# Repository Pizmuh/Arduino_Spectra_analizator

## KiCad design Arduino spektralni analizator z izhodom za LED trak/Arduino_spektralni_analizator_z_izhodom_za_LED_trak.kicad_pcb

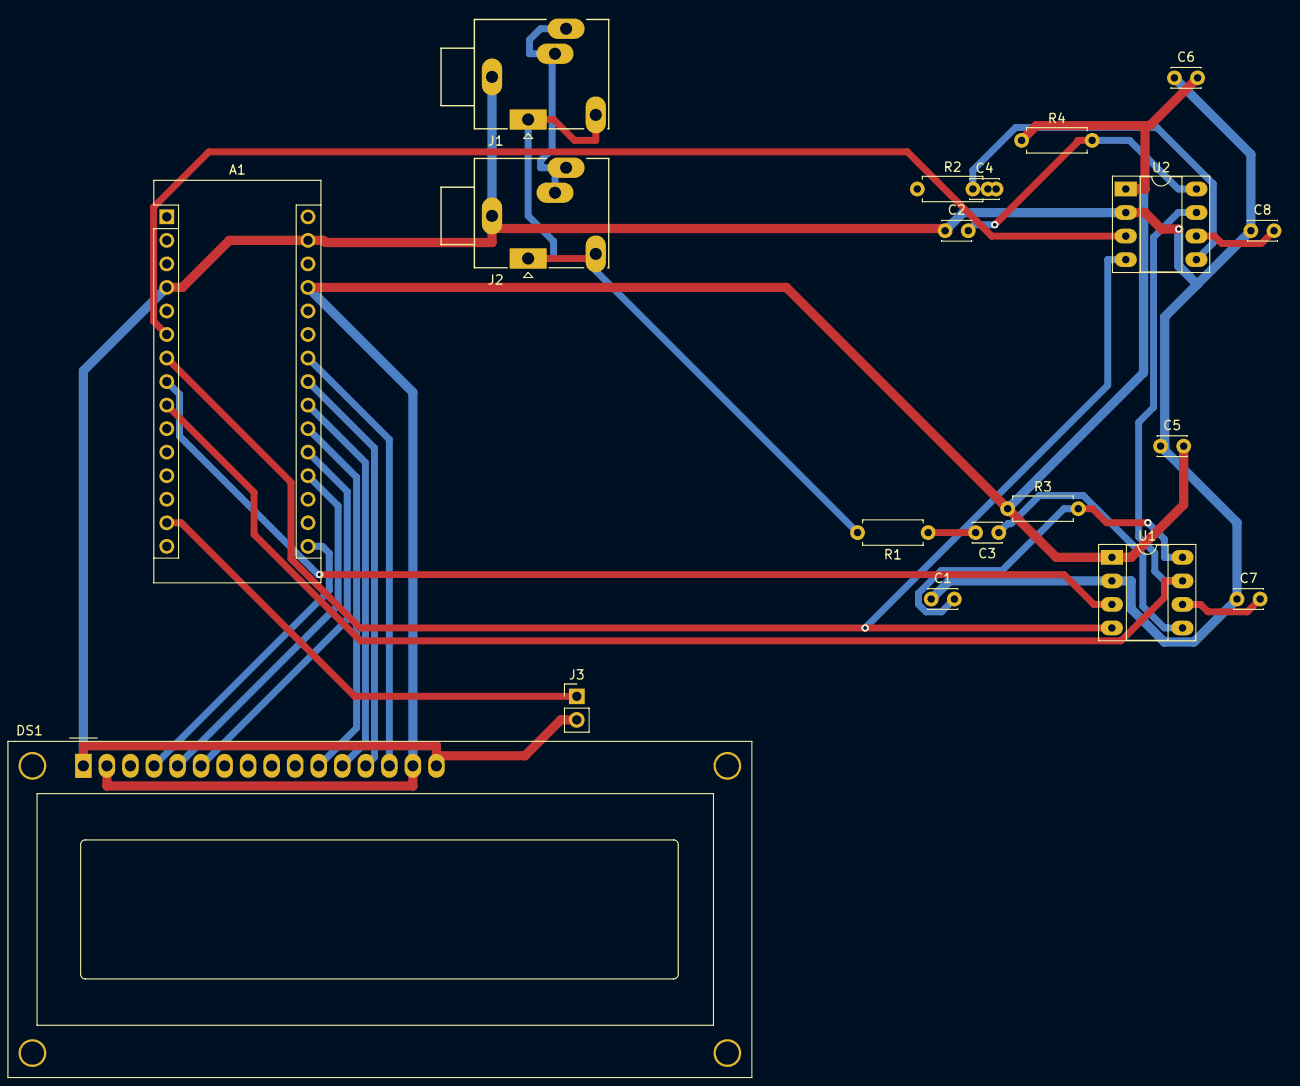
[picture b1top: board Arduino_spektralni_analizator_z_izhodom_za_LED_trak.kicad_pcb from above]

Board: 2 copper layers, 19 parts (0 on the bottom side), 24 nets.

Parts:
A1: Arduino_Nano_v3.x; Arduino_Nano
C1, C2: 33pF; C_Disc_D3.0mm_W2.0mm_P2.50mm
C3, C4: 10nF; C_Disc_D3.0mm_W2.0mm_P2.50mm
C5, C6: 0.1uF; C_Disc_D3.0mm_W2.0mm_P2.50mm
C7, C8: 0.1 uF; C_Disc_D3.0mm_W2.0mm_P2.50mm
DS1: WC1602A
J1, J2: AudioJack3_SwitchTR; Jack_3.5mm_Ledino_KB3SPRS_Horizontal
J3: Conn_01x02_Male; PinHeader_1x02_P2.54mm_Vertical
R1, R2: 22k; R_Axial_DIN0207_L6.3mm_D2.5mm_P7.62mm_Horizontal
R3, R4: 200k; R_Axial_DIN0207_L6.3mm_D2.5mm_P7.62mm_Horizontal
U1, U2: MSGEQ7; DIP-8_W7.62mm_Socket_LongPads

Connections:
/LCD_D4: A1.21 (A2), DS1.11 (D4)
/LCD_D5: A1.22 (A3), DS1.12 (D5)
/LCD_D6: A1.23 (A4), DS1.13 (D6)
/LCD_D7: A1.24 (A5), DS1.14 (D7)
/LCD_EN: A1.20 (A1), DS1.6 (E)
/LCD_RS: A1.16 (D13), DS1.4 (RS)
/LCD_RW: A1.19 (A0), DS1.5 (R/W)
/MSGEQ7_DATA_L: A1.6 (D3), U2.3 (OUT)
/MSGEQ7_DATA_R: A1.8 (D5), U1.3 (OUT)
/MSGEQ7_RESET: A1.9 (D6), U1.7 (RESET), U2.7 (RESET)
/MSGEQ7_STROBE: A1.7 (D4), U1.4 (STROBE), U2.4 (STROBE)
/SPK_LEFT: J1.R, J1.RN, J2.R, J2.RN, R2.2
/SPK_RIGHT: J1.T, J1.TN, J2.T, J2.TN, R1.2
/WS2813_DRIVE: A1.14 (D11), J3.1
GND: A1.4 (GND), A1.29 (GND), C1.1, C2.1, C5.1, C6.1, C7.1, C8.1, DS1.1 (VSS), DS1.16 (LED(-)), J1.S, J2.S, J3.2, U1.2 (VSS), U2.2 (VSS)
unnamed: C1.2, R3.2, U1.8 (CKIN)
unnamed: C2.2, R4.2, U2.8 (CKIN)
unnamed: C3.1, U1.5 (IN)
unnamed: C3.2, R1.1
unnamed: C4.1, U2.5 (IN)
unnamed: C4.2, R2.1
unnamed: C7.2, U1.6 (GND)
unnamed: C8.2, U2.6 (GND)
VCC: A1.27 (+5V), C5.2, C6.2, DS1.2 (VDD), DS1.15 (LED(+)), R3.1, R4.1, U1.1 (VDD), U2.1 (VDD)
